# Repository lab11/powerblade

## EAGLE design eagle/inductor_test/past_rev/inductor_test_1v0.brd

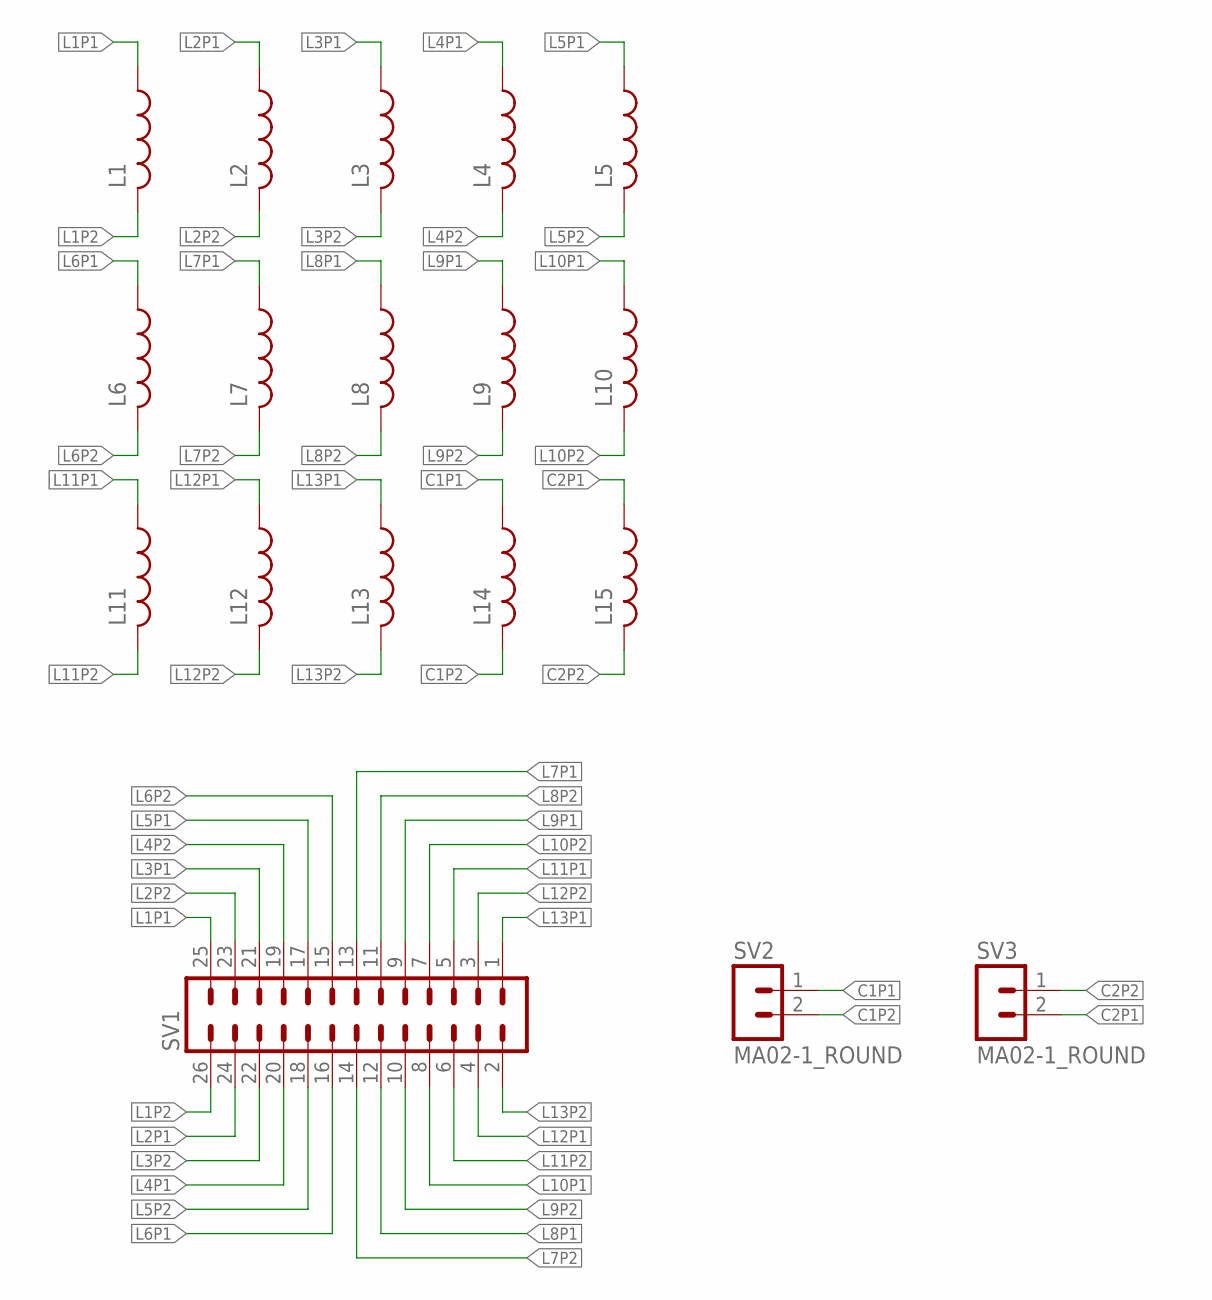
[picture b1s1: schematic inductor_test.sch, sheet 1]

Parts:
L1, L2, L3, L4, L5, L6, L7, L8, L9, L10, L11, L12, L13, L14, L15: L-USL0805; L0805
SV1: MA13-2BARE; MA13-2_BARE; DIGIKEY 3M9464-ND
SV2, SV3: MA02-1_ROUND; DIGIKEY NP

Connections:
C1P1: L14.1, SV2.1
C1P2: L14.2, SV2.2
C2P1: L15.1, SV3.2
C2P2: L15.2, SV3.1
L1P1: L1.1, SV1.25
L1P2: L1.2, SV1.26
L2P1: L2.1, SV1.24
L2P2: L2.2, SV1.23
L3P1: L3.1, SV1.21
L3P2: L3.2, SV1.22
L4P1: L4.1, SV1.20
L4P2: L4.2, SV1.19
L5P1: L5.1, SV1.17
L5P2: L5.2, SV1.18
L6P1: L6.1, SV1.16
L6P2: L6.2, SV1.15
L7P1: L7.1, SV1.13
L7P2: L7.2, SV1.14
L8P1: L8.1, SV1.12
L8P2: L8.2, SV1.11
L9P1: L9.1, SV1.9
L9P2: L9.2, SV1.10
L10P1: L10.1, SV1.8
L10P2: L10.2, SV1.7
L11P1: L11.1, SV1.5
L11P2: L11.2, SV1.6
L12P1: L12.1, SV1.4
L12P2: L12.2, SV1.3
L13P1: L13.1, SV1.1
L13P2: L13.2, SV1.2

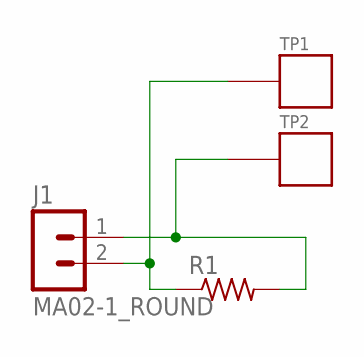
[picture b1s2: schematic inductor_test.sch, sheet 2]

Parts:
J1: MA02-1_ROUND; DIGIKEY NP
R1: R-US_R0603; R0603; DIGIKEY P49.9HCT-ND
TP1, TP2: TP_STD; TP; DIGIKEY NP

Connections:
unnamed: J1.2, R1.1, TP1.P$1
unnamed: J1.1, R1.2, TP2.P$1

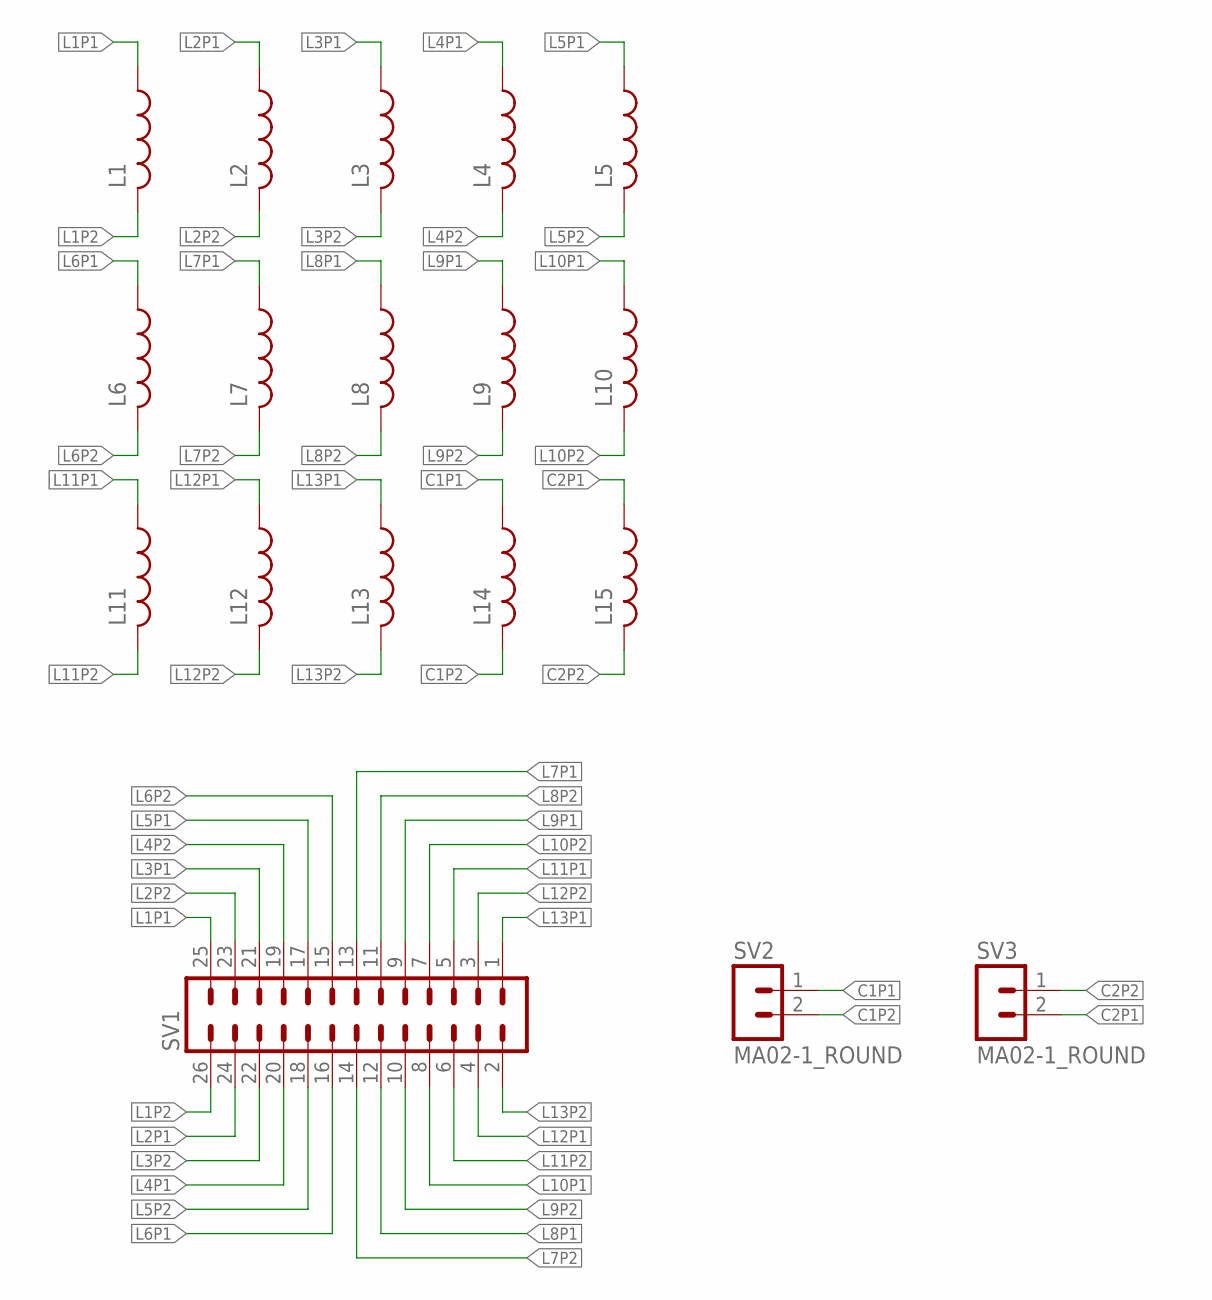
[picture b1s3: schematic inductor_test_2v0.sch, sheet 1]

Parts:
L1, L2, L3, L4, L5, L6, L7, L8, L9, L10, L11, L12, L13, L14, L15: L-USL0805; L0805
SV1: MA13-2BARE; MA13-2_BARE; DIGIKEY 3M9464-ND
SV2, SV3: MA02-1_ROUND; DIGIKEY NP

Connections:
C1P1: L14.1, SV2.1
C1P2: L14.2, SV2.2
C2P1: L15.1, SV3.2
C2P2: L15.2, SV3.1
L1P1: L1.1, SV1.25
L1P2: L1.2, SV1.26
L2P1: L2.1, SV1.24
L2P2: L2.2, SV1.23
L3P1: L3.1, SV1.21
L3P2: L3.2, SV1.22
L4P1: L4.1, SV1.20
L4P2: L4.2, SV1.19
L5P1: L5.1, SV1.17
L5P2: L5.2, SV1.18
L6P1: L6.1, SV1.16
L6P2: L6.2, SV1.15
L7P1: L7.1, SV1.13
L7P2: L7.2, SV1.14
L8P1: L8.1, SV1.12
L8P2: L8.2, SV1.11
L9P1: L9.1, SV1.9
L9P2: L9.2, SV1.10
L10P1: L10.1, SV1.8
L10P2: L10.2, SV1.7
L11P1: L11.1, SV1.5
L11P2: L11.2, SV1.6
L12P1: L12.1, SV1.4
L12P2: L12.2, SV1.3
L13P1: L13.1, SV1.1
L13P2: L13.2, SV1.2

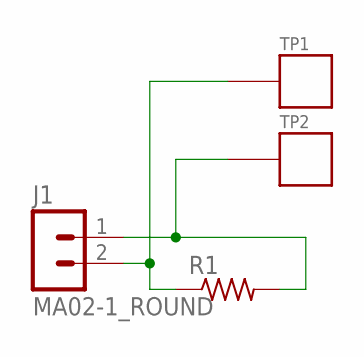
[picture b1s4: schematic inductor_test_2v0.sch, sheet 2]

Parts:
J1: MA02-1_ROUND; DIGIKEY NP
R1: R-US_R0603; R0603; DIGIKEY P49.9HCT-ND
TP1, TP2: TP_STD; TP; DIGIKEY NP

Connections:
unnamed: J1.2, R1.1, TP1.P$1
unnamed: J1.1, R1.2, TP2.P$1

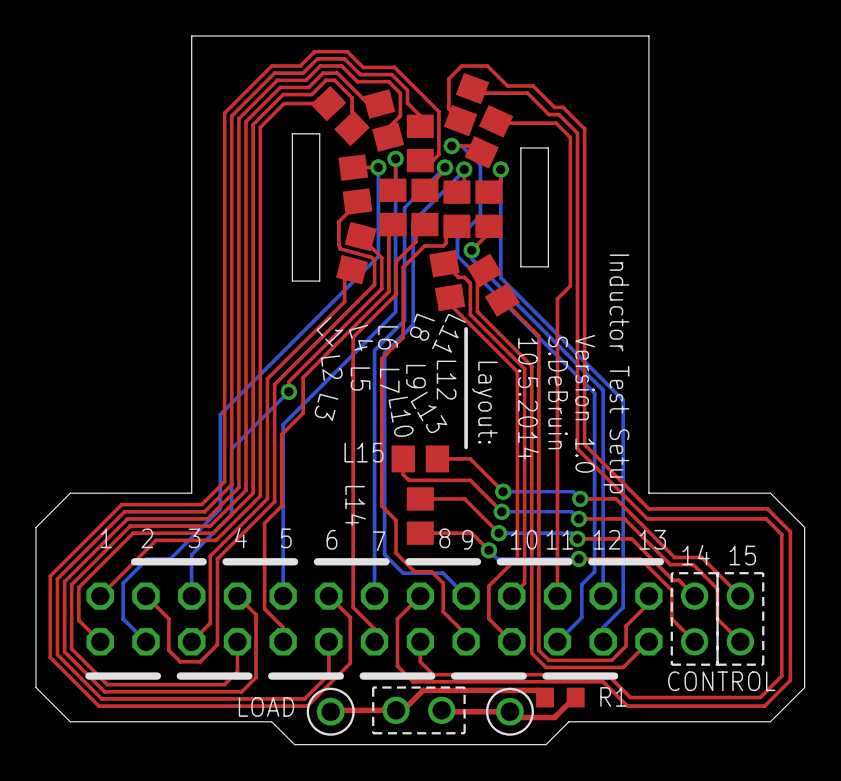
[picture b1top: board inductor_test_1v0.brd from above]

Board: 2 copper layers, 42.7 x 39.4 mm, 23 parts (0 on the bottom side), 32 nets.

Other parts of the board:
U$1: NEMA_1-15_TIGHT

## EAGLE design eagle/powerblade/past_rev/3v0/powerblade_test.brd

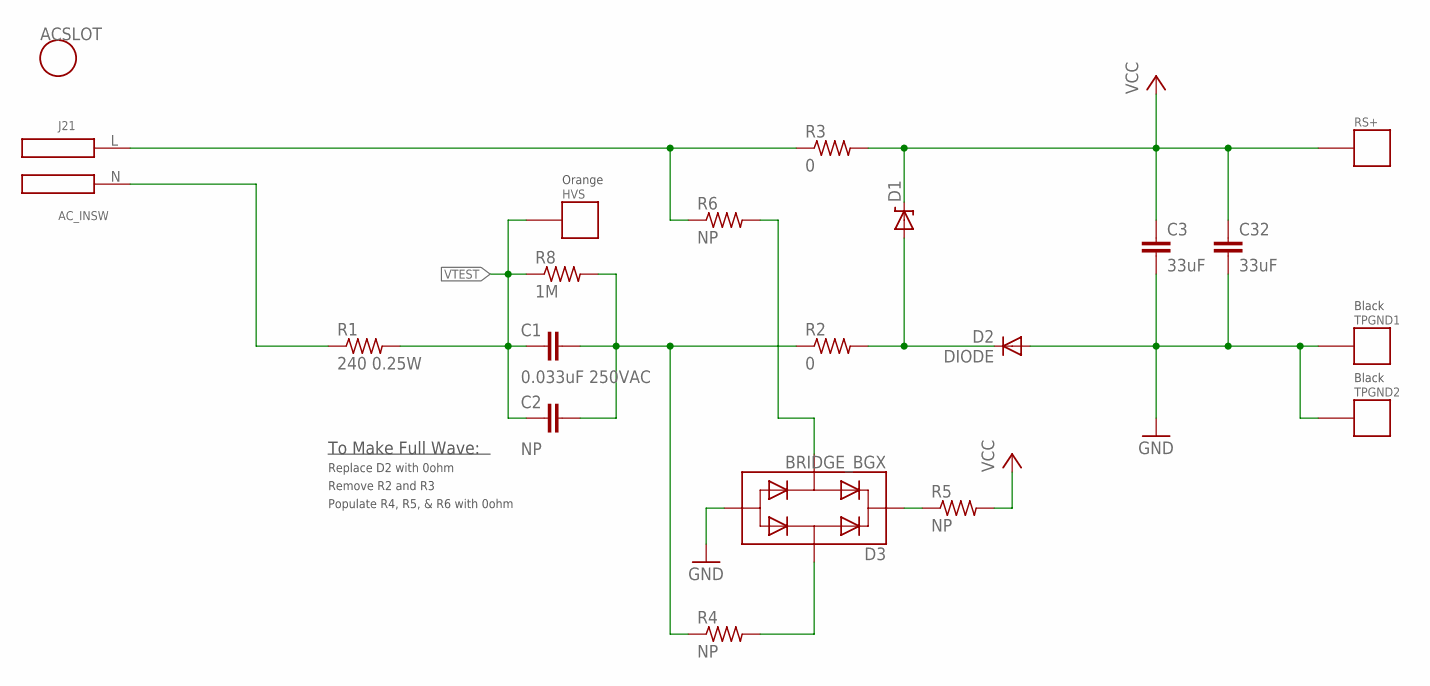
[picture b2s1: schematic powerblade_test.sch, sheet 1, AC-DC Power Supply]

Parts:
ACSLOT: AC_NODIM; AC3_NODIM; DIGIKEY NP
C1: 0.033uF 250VAC; C2220K; DIGIKEY 490-5919-1-ND
C2: NP; C2220K; DIGIKEY NP
C3, C32: 33uF; C0603; DIGIKEY 718-1672-1-ND
D1: ZENERBZT52; BZT52; DIGIKEY NP
D2: DIODE; BAS521; DIGIKEY NP
D3: BRIDGE_BGX; TO-253-4; DIGIKEY NP
HVS: TP_MULT; DIGIKEY 5013K-ND
J21: AC_INSW; AC_DC21; DIGIKEY NP
R1: 240 0.25W; R0603; DIGIKEY RHM240DCT-ND
R2, R3: 0; R0603; DIGIKEY P0.0GCT-ND
R4, R5, R6: NP; R0603; DIGIKEY NP
R8: 1M; R0603; DIGIKEY MCT0603-1.00M-CFCT-ND
RS+: TP_MULT; DIGIKEY 5014K-ND
TPGND1, TPGND2: TP_MULT; DIGIKEY 5011K-ND

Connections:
GND: C3.2, C32.2, D2.A, D3.P3, TPGND1.P$1, TPGND2.P$1; also elsewhere on the board
N: J21.N, R1.1
unnamed: D1.A, D2.C, R2.2
unnamed: C1.1, C2.1, R2.1, R4.1, R8.2
unnamed: D3.P4, R4.2
unnamed: D3.P1, R5.1
unnamed: D3.P2, R6.2
P: J21.L, R3.1, R6.1
VCC: C3.1, C32.1, D1.C, R3.2, R5.2, RS+.P$1; also elsewhere on the board
VTEST: C1.2, C2.2, HVS.P$1, R1.2, R8.1; also elsewhere on the board

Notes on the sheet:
To Make Full Wave:
Replace D2 with 0ohm
Remove R2 and R3
Populate R4, R5, & R6 with 0ohm
Orange
Black

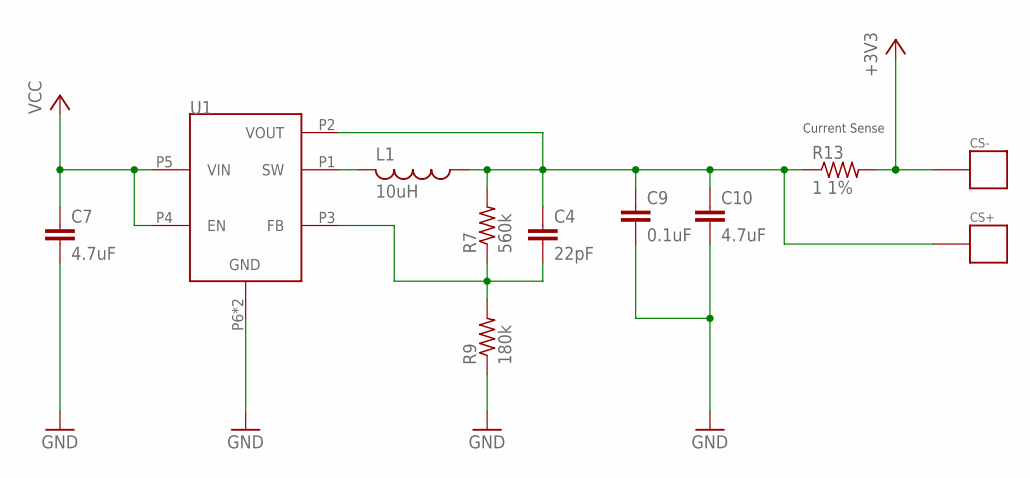
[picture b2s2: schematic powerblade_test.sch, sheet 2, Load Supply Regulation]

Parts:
C4: 22pF; C0402; DIGIKEY 1276-1116-1-ND
C7: 4.7uF; C0603; DIGIKEY 1276-1784-1-ND
C9: 0.1uF; C0402; DIGIKEY 1276-1001-1-ND
C10: 4.7uF; C0402; DIGIKEY 490-5915-1-ND
CS+: TP_MULT; DIGIKEY 5012K-ND
CS-: TP_MULT; DIGIKEY 5010K-ND
L1: 10uH; L0805; DIGIKEY 490-4990-1-ND
R7: 560k; R0402; DIGIKEY P560KLCT-ND
R9: 180k; R0402; DIGIKEY P180KLCT-ND
R13: 1 1%; R0603; DIGIKEY P1.0AJCT-ND
U1: TPS62122; WDFN-6

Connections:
+3V3: CS-.P$1, R13.2; also elsewhere on the board
GND: C7.2, C9.2, C10.2, R9.1, U1.P6 (GND), U1.PAD (GND); also elsewhere on the board
unnamed: L1.2, U1.P1 (SW)
unnamed: C4.1, C9.1, C10.1, CS+.P$1, L1.1, R7.2, R13.1, U1.P2 (VOUT)
unnamed: C4.2, R7.1, R9.2, U1.P3 (FB)
VCC: C7.1, U1.P4 (EN), U1.P5 (VIN); also elsewhere on the board

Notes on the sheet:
Current Sense

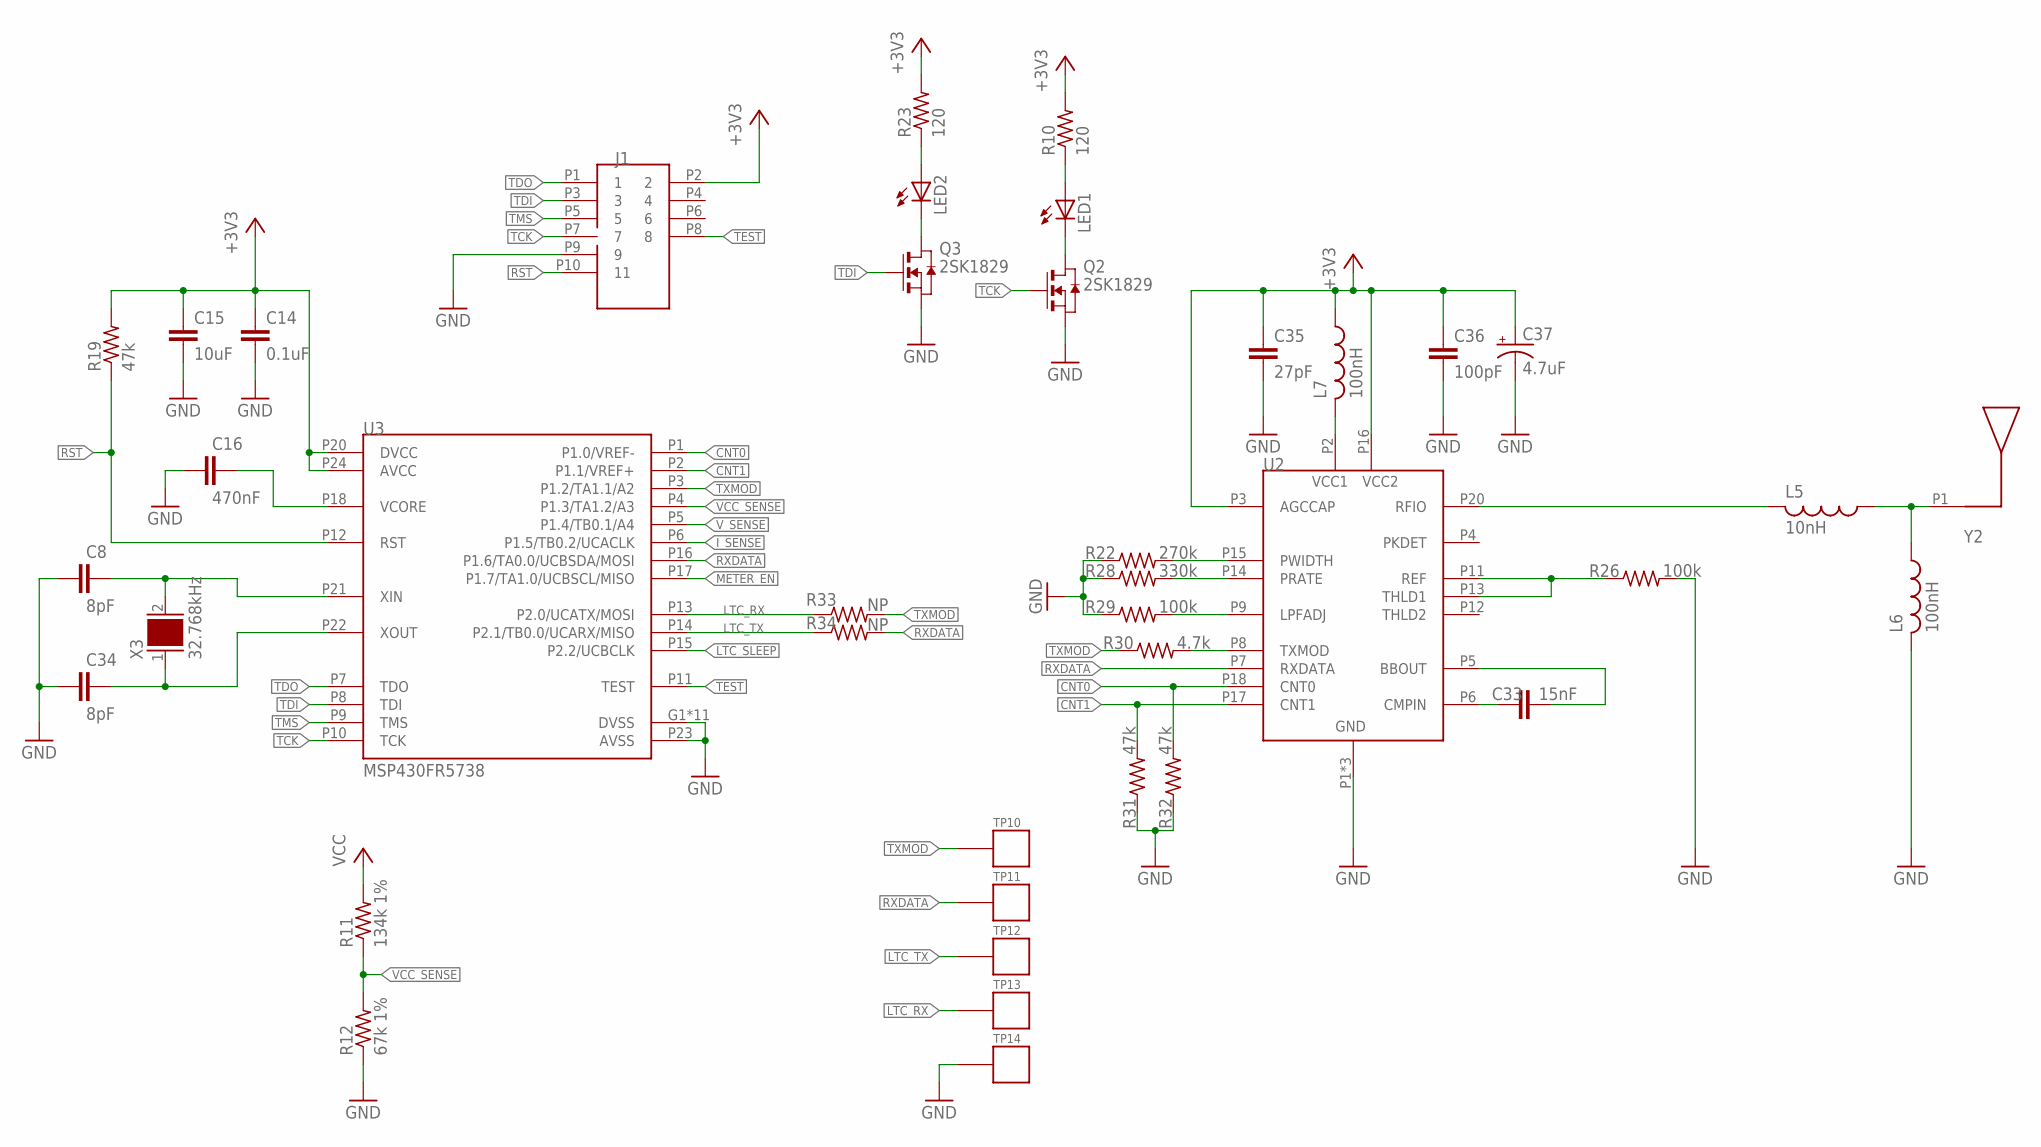
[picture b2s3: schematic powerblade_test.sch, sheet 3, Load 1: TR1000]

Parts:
C8, C34: 8pF; C0603; DIGIKEY 1276-1817-1-ND
C14: 0.1uF; C0603; DIGIKEY 445-1316-1-ND
C15: 10uF; C0603; DIGIKEY 1276-1119-1-ND
C16: 470nF; C0603; DIGIKEY 445-5192-1-ND
C33: 15nF; C0603; DIGIKEY 445-5091-1-ND
C35: 27pF; C0603; DIGIKEY 445-1274-1-ND
C36: 100pF; C0603; DIGIKEY 445-1281-1-ND
C37: 4.7uF; CPOL-0805; DIGIKEY 478-8120-1-ND
J1: JTAG_14PIN_IDC; TC2050-IDC-430; DIGIKEY NP
L5: 10nH; L0402; DIGIKEY 732-2924-1-ND
L6: 100nH; L0402; DIGIKEY CW100505-R10JCT-ND
L7: 100nH; L0603; DIGIKEY 587-1566-1-ND
LED1, LED2: LED0603; LED-0603; DIGIKEY 160-1183-1-ND
Q2, Q3: 2SK1829; SC-70-3
R10, R23: 120; R0603; DIGIKEY P120GCT-ND
R11: 134k 1%; R0603; DIGIKEY P133KHCT-ND
R12: 67k 1%; R0603; DIGIKEY P66.5KHCT-ND
R19, R31, R32: 47k; R0603; DIGIKEY P47KGCT-ND
R22: 270k; R0603; DIGIKEY P270KGCT-ND
R26, R29: 100k; R0603; DIGIKEY P100KGCT-ND
R28: 330k; R0603; DIGIKEY P330KGCT-ND
R30: 4.7k; R0603; DIGIKEY P4.7KGCT-ND
R33, R34: NP; R0603; DIGIKEY NP
TP10, TP11, TP12, TP13, TP14: TP_STD; TP; DIGIKEY NP
U2: TR1000; SM-20H
U3: MSP430FR5738; VQFN-24
X3: 32.768kHz; 0805; DIGIKEY 535-12373-1-ND
Y2: ANT-916

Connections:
+3V3: C14.1, C15.1, C35.1, C36.1, C37.+, J1.P2 (2), L7.1, R10.2, R19.2, R23.2, U2.P3 (AGCCAP), U2.P16 (VCC2), U3.P20 (DVCC), U3.P24 (AVCC); also elsewhere on the board
CNT0: R32.2, U2.P18 (CNT0), U3.P1 (P1.0/VREF-)
CNT1: R31.2, U2.P17 (CNT1), U3.P2 (P1.1/VREF+)
GND: C8.1, C14.2, C15.2, C16.1, C34.1, C35.2, C36.2, C37.-, J1.P9 (9), L6.2, Q2.P2 (S), Q3.P2 (S), R12.1, R22.1, R26.2, R28.1, R29.1, R31.1, R32.1, TP14.P$1, U2.P1 (GND), U2.P10 (GND), U2.P19 (GND), U3.G1 (DVSS), U3.G2 (DVSS), U3.G3 (DVSS), U3.G4 (DVSS), U3.G5 (DVSS), U3.G6 (DVSS), U3.G7 (DVSS), U3.G8 (DVSS), U3.G9 (DVSS), U3.P19 (DVSS), U3.P23 (AVSS), U3.PAD (DVSS); also elsewhere on the board
I_SENSE: U3.P6 (P1.5/TB0.2/UCACLK); also elsewhere on the board
LTC_RX: R33.1, TP13.P$1, U3.P13 (P2.0/UCATX/MOSI); also elsewhere on the board
LTC_SLEEP: U3.P15 (P2.2/UCBCLK); also elsewhere on the board
LTC_TX: R34.1, TP12.P$1, U3.P14 (P2.1/TB0.0/UCARX/MISO); also elsewhere on the board
METER_EN: U3.P17 (P1.7/TA1.0/UCBSCL/MISO); also elsewhere on the board
unnamed: C34.2, U3.P22 (XOUT), X3.1
unnamed: C33.2, U2.P5 (BBOUT)
unnamed: L7.2, U2.P2 (VCC1)
unnamed: C16.2, U3.P18 (VCORE)
unnamed: LED1.A, R10.1
unnamed: R22.2, U2.P15 (PWIDTH)
unnamed: R28.2, U2.P14 (PRATE)
unnamed: R29.2, U2.P9 (LPFADJ)
unnamed: R30.2, U2.P8 (TXMOD)
unnamed: LED1.C, Q2.P3 (D)
unnamed: C33.1, U2.P6 (CMPIN)
unnamed: C8.2, U3.P21 (XIN), X3.2
unnamed: R26.1, U2.P11 (REF), U2.P13 (THLD1)
unnamed: LED2.A, R23.1
unnamed: LED2.C, Q3.P3 (D)
unnamed: L5.2, U2.P20 (RFIO)
unnamed: L5.1, L6.1, Y2.P1
RST: J1.P10 (11), R19.1, U3.P12 (RST)
RXDATA: R34.2, TP11.P$1, U2.P7 (RXDATA), U3.P16 (P1.6/TA0.0/UCBSDA/MOSI)
TCK: J1.P7 (7), Q2.P1 (G), U3.P10 (TCK)
TDI: J1.P3 (3), Q3.P1 (G), U3.P8 (TDI)
TDO: J1.P1 (1), U3.P7 (TDO)
TEST: J1.P8 (8), U3.P11 (TEST)
TMS: J1.P5 (5), U3.P9 (TMS)
TXMOD: R30.1, R33.2, TP10.P$1, U3.P3 (P1.2/TA1.1/A2)
VCC: R11.2; also elsewhere on the board
VCC_SENSE: R11.1, R12.2, U3.P4 (P1.3/TA1.2/A3)
V_SENSE: U3.P5 (P1.4/TB0.1/A4); also elsewhere on the board

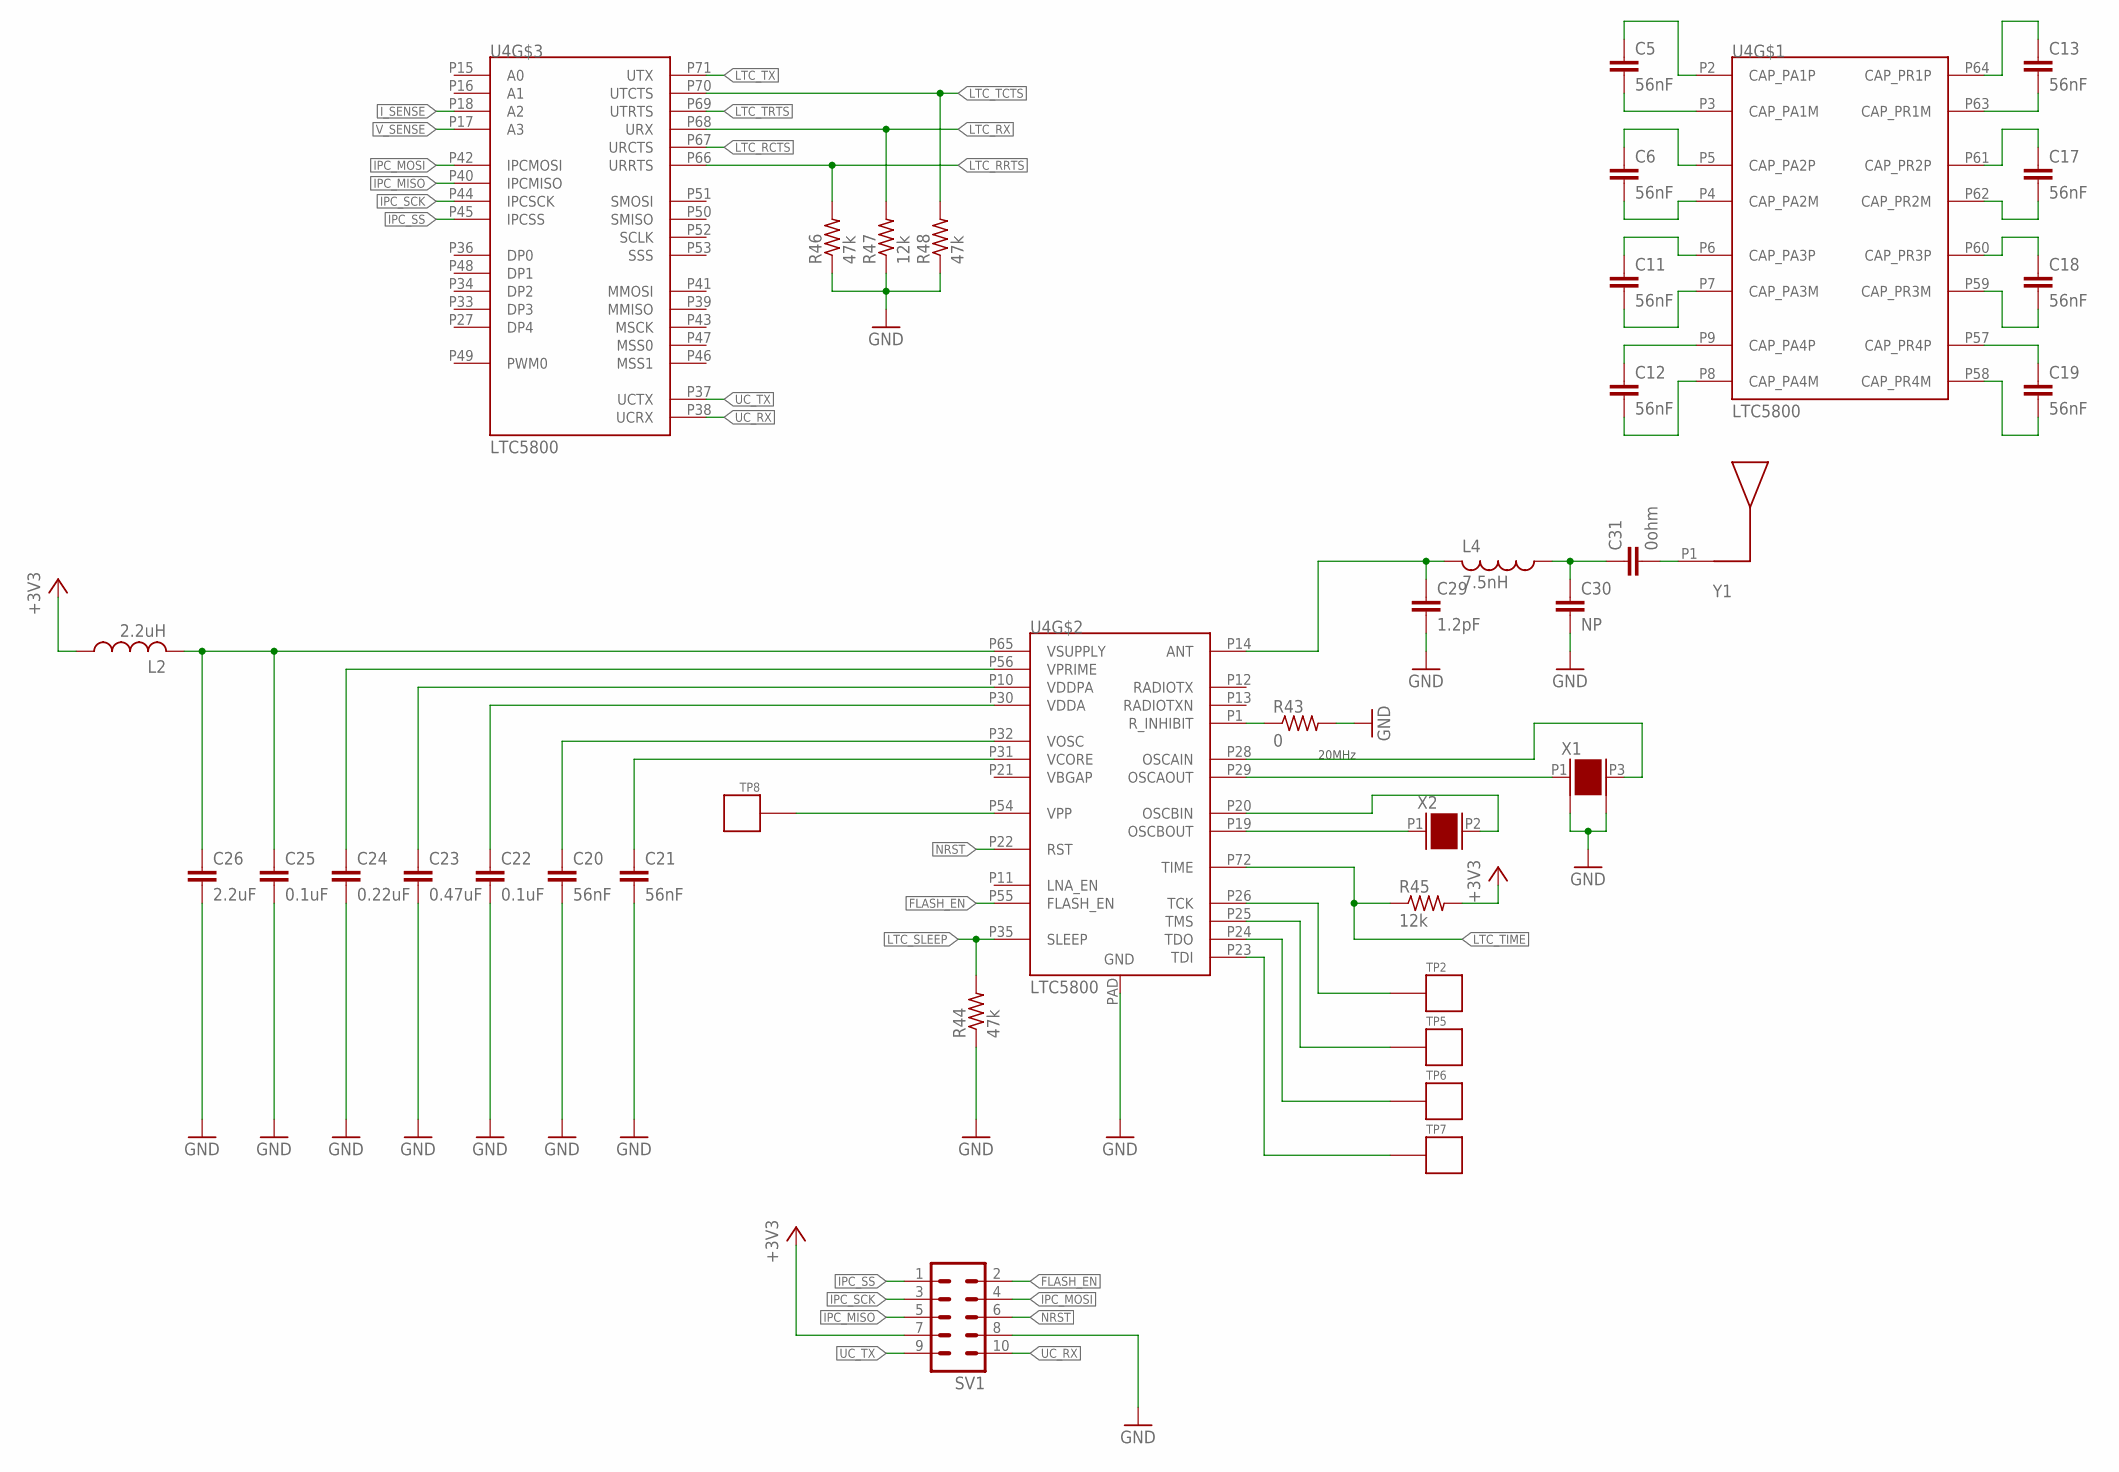
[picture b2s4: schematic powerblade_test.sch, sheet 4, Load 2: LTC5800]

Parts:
C5, C6, C11, C12, C13, C17, C18, C19, C20, C21: 56nF; C0402; DIGIKEY 490-6324-1-ND
C22, C25: 0.1uF; C0603; DIGIKEY 445-1316-1-ND
C23: 0.47uF; C0603; DIGIKEY 1276-2377-1-ND
C24: 0.22uF; C0603; DIGIKEY 445-1318-1-ND
C26: 2.2uF; C0603; DIGIKEY 1276-2368-1-ND
C29: 1.2pF; C0402; DIGIKEY 490-6209-1-ND
C30: NP; C0402; DIGIKEY NP
C31: 0ohm; C0402; DIGIKEY P0.0JCT-ND
L2: 2.2uH; L0603; DIGIKEY 490-4023-1-ND
L4: 7.5nH; L0402; DIGIKEY 490-6760-1-ND
R43: 0; R0402; DIGIKEY P0.0JCT-ND
R44, R46, R48: 47k; R0402; DIGIKEY P47KJCT-ND
R45, R47: 12k; R0402; DIGIKEY P12KJCT-ND
SV1: MA05-2KEY; MA05-2_KEY
TP2, TP5, TP6, TP7: TP_SMD; DIGIKEY NP
TP8: TP_STD; TP; DIGIKEY NP
U4: LTC5800; QFN-72
X1: ABM8G
X2: ABS07
Y1: UREACH_XTEND

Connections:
+3V3: L2.1, R45.2, SV1.7; also elsewhere on the board
FLASH_EN: SV1.2, U4.P55 (FLASH_EN)
GND: C20.2, C21.2, C22.2, C23.2, C24.2, C25.2, C26.2, C29.2, C30.2, R43.2, R44.1, R46.1, R47.1, R48.1, SV1.8, U4.PAD (GND), X1.P2 (G1), X1.P4 (G2); also elsewhere on the board
IPC_MISO: SV1.5, U4.P40 (IPCMISO)
IPC_MOSI: SV1.4, U4.P42 (IPCMOSI)
IPC_SCK: SV1.3, U4.P44 (IPCSCK)
IPC_SS: SV1.1, U4.P45 (IPCSS)
I_SENSE: U4.P18 (A2); also elsewhere on the board
LTC_RCTS: U4.P67 (URCTS)
LTC_RRTS: R46.2, U4.P66 (URRTS)
LTC_RX: R47.2, U4.P68 (URX); also elsewhere on the board
LTC_SLEEP: R44.2, U4.P35 (SLEEP); also elsewhere on the board
LTC_TCTS: R48.2, U4.P70 (UTCTS)
LTC_TIME: R45.1, U4.P72 (TIME)
LTC_TRTS: U4.P69 (UTRTS)
LTC_TX: U4.P71 (UTX); also elsewhere on the board
unnamed: C5.1, U4.P2 (CAP_PA1P)
unnamed: C5.2, U4.P3 (CAP_PA1M)
unnamed: C6.1, U4.P5 (CAP_PA2P)
unnamed: C6.2, U4.P4 (CAP_PA2M)
unnamed: C11.1, U4.P6 (CAP_PA3P)
unnamed: C11.2, U4.P7 (CAP_PA3M)
unnamed: C12.1, U4.P9 (CAP_PA4P)
unnamed: C12.2, U4.P8 (CAP_PA4M)
unnamed: C13.1, U4.P64 (CAP_PR1P)
unnamed: C13.2, U4.P63 (CAP_PR1M)
unnamed: C17.1, U4.P61 (CAP_PR2P)
unnamed: C17.2, U4.P62 (CAP_PR2M)
unnamed: C18.1, U4.P60 (CAP_PR3P)
unnamed: C18.2, U4.P59 (CAP_PR3M)
unnamed: C19.1, U4.P57 (CAP_PR4P)
unnamed: C19.2, U4.P58 (CAP_PR4M)
unnamed: C21.1, U4.P31 (VCORE)
unnamed: C20.1, U4.P32 (VOSC)
unnamed: C25.1, C26.1, L2.2, U4.P65 (VSUPPLY)
unnamed: C24.1, U4.P56 (VPRIME)
unnamed: C23.1, U4.P10 (VDDPA)
unnamed: C22.1, U4.P30 (VDDA)
unnamed: U4.P29 (OSCAOUT), X1.P1
unnamed: U4.P28 (OSCAIN), X1.P3 (P2)
unnamed: U4.P20 (OSCBIN), X2.P2
unnamed: U4.P19 (OSCBOUT), X2.P1
unnamed: C29.1, L4.2, U4.P14 (ANT)
unnamed: C30.1, C31.1, L4.1
unnamed: C31.2, Y1.P1
unnamed: TP8.P$1, U4.P54 (VPP)
unnamed: TP7.P$1, U4.P23 (TDI)
unnamed: TP6.P$1, U4.P24 (TDO)
unnamed: TP5.P$1, U4.P25 (TMS)
unnamed: TP2.P$1, U4.P26 (TCK)
unnamed: R43.1, U4.P1 (R_INHIBIT)
NRST: SV1.6, U4.P22 (RST)
UC_RX: SV1.10, U4.P38 (UCRX)
UC_TX: SV1.9, U4.P37 (UCTX)
V_SENSE: U4.P17 (A3); also elsewhere on the board

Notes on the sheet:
20MHz

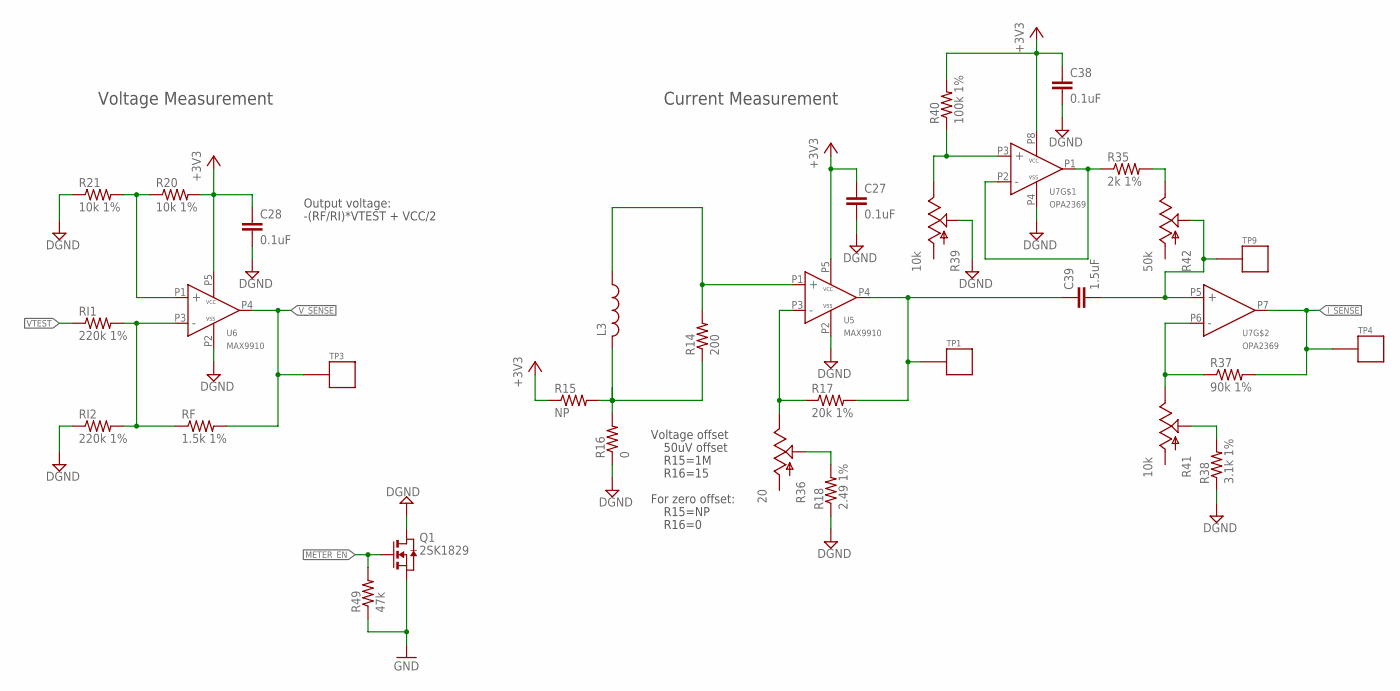
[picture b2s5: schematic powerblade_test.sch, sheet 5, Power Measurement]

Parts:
C27, C28, C38: 0.1uF; C0402; DIGIKEY 445-1265-1-ND
C39: 1.5uF; C0402; DIGIKEY 445-13874-1-ND
L3: L-USL0805; L0805; DIGIKEY 732-3452-1-ND
Q1: 2SK1829; SC-70-3
R14: 200; R0402; DIGIKEY P200LCT-ND
R15: NP; R0402; DIGIKEY NP
R16: 0; R0402; DIGIKEY P0.0JCT-ND
R17: 20k 1%; R0402; DIGIKEY P20.0KLCT-ND
R18: 2.49 1%; R0402; DIGIKEY 541-2.49LLCT-ND
R20, R21: 10k 1%; R0402; DIGIKEY P10.0KLCT-ND
R35: 2k 1%; R0402; DIGIKEY P2.00KLCT-ND
R36: 20; 3313_POT; DIGIKEY 3313J-1-200ECT-ND
R37: 90k 1%; R0402; DIGIKEY P90.9KLCT-ND
R38: 3.1k 1%; R0603; DIGIKEY P3.09KHCT-ND
R39, R41: 10k; 3313_POT; DIGIKEY 3313J-103ECT-ND
R40: 100k 1%; R0402; DIGIKEY P100KLCT-ND
R42: 50k; 3313_POT; DIGIKEY 3313J-503ECT-ND
R49: 47k; R0603; DIGIKEY P47KGCT-ND
RF: 1.5k 1%; R0402; DIGIKEY P1.50KLCT-ND
RI1, RI2: 220k 1%; R0402; DIGIKEY P220KLCT-ND
TP1, TP4, TP9: TP_MULT; DIGIKEY 5126K-ND
TP3: TP_MULT; DIGIKEY 5129K-ND
U5, U6: MAX9910; SC70-5
U7: OPA2369; SOT-23-8

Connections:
+3V3: C27.1, C28.1, C38.1, R15.1, R20.2, R40.2, U5.P5 (VCC), U6.P5 (VCC), U7.P8 (VCC); also elsewhere on the board
DGND: C27.2, C28.2, C38.2, Q1.P3 (D), R16.1, R18.1, R21.1, R38.1, R39.PW, RI2.1, U5.P2 (VSS), U6.P2 (VSS), U7.P4 (VSS)
GND: Q1.P2 (S), R49.1; also elsewhere on the board
I_SENSE: R37.2, TP4.P$1, U7.P7 (OUT); also elsewhere on the board
METER_EN: Q1.P1 (G), R49.2; also elsewhere on the board
unnamed: L3.2, R14.1, R15.2, R16.2
unnamed: L3.1, R14.2, U5.P1 (IN+)
unnamed: R17.1, R36.P2, U5.P3 (IN-)
unnamed: R20.1, R21.2, U6.P1 (IN+)
unnamed: RF.1, RI1.2, RI2.2, U6.P3 (IN-)
unnamed: C39.1, R17.2, TP1.P$1, U5.P4 (OUT)
unnamed: R18.2, R36.PW
unnamed: R37.1, R41.P2, U7.P6 (IN-)
unnamed: C39.2, R42.PW, TP9.P$1, U7.P5 (IN+)
unnamed: R35.1, U7.P1 (OUT), U7.P2 (IN-)
unnamed: R38.2, R41.PW
unnamed: R39.P2, R40.1, U7.P3 (IN+)
unnamed: R35.2, R42.P2
VTEST: RI1.1; also elsewhere on the board
V_SENSE: RF.2, TP3.P$1, U6.P4 (OUT); also elsewhere on the board

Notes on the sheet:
Voltage offset
50uV offset
For zero offset:
R15=NP
R16=0
Current Measurement
Voltage Measurement
Output voltage:
-(RF/RI)*VTEST + VCC/2
R15=1M
R16=15

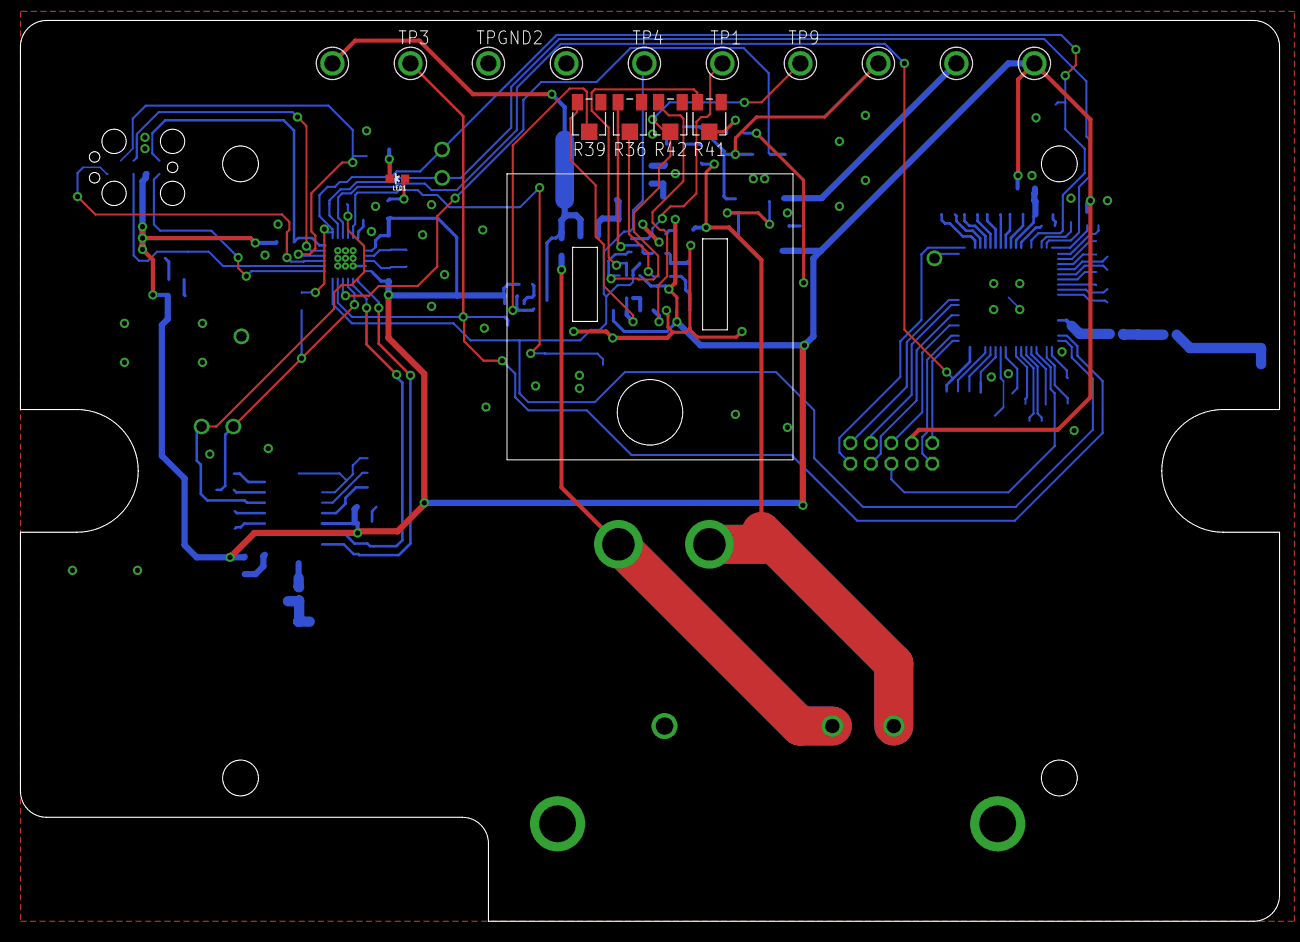
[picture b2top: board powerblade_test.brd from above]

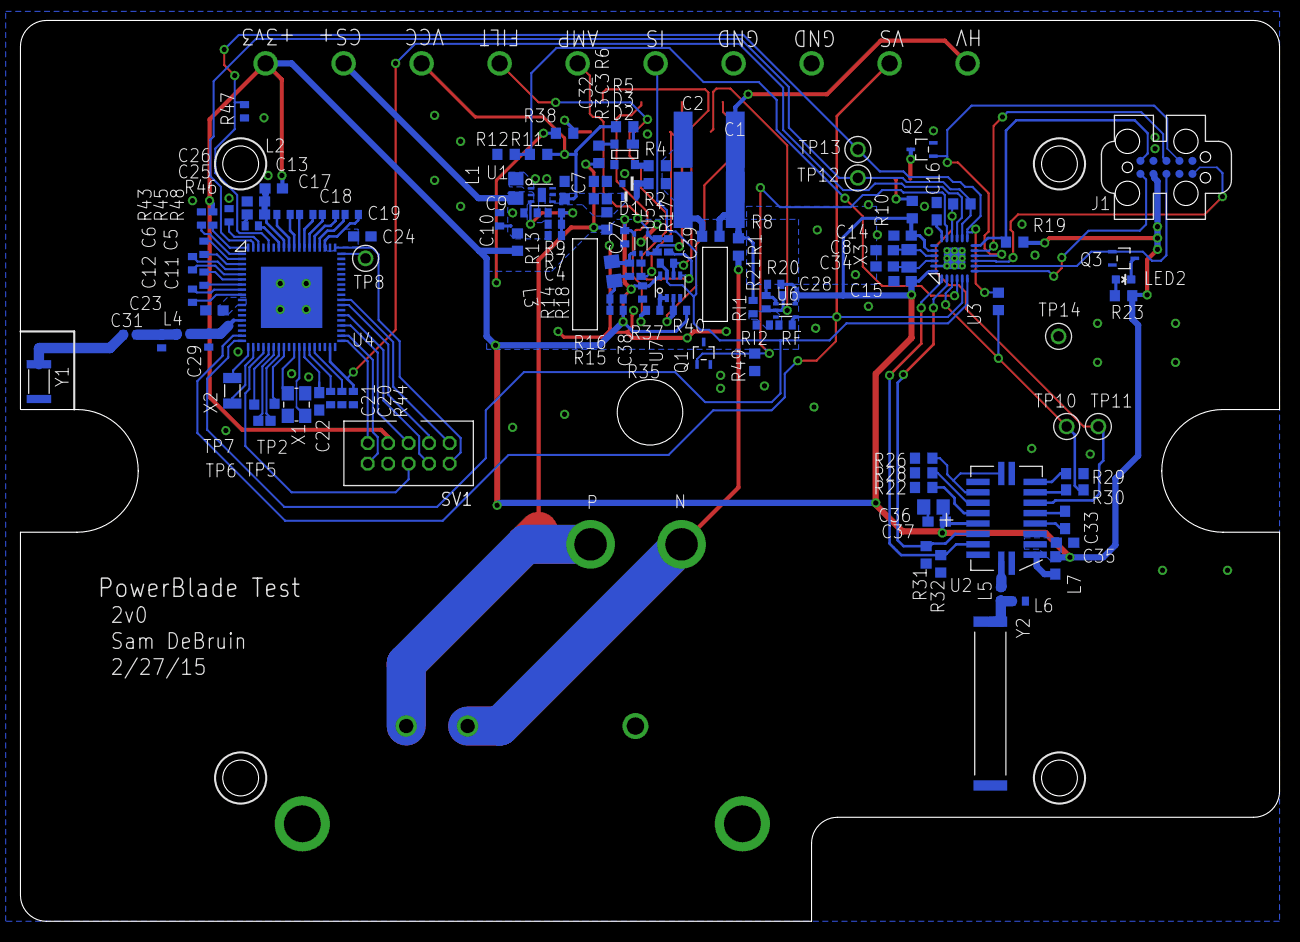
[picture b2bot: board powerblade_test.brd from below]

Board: 2 copper layers, 123.0 x 88.0 mm, 139 parts (123 on the bottom side), 108 nets.

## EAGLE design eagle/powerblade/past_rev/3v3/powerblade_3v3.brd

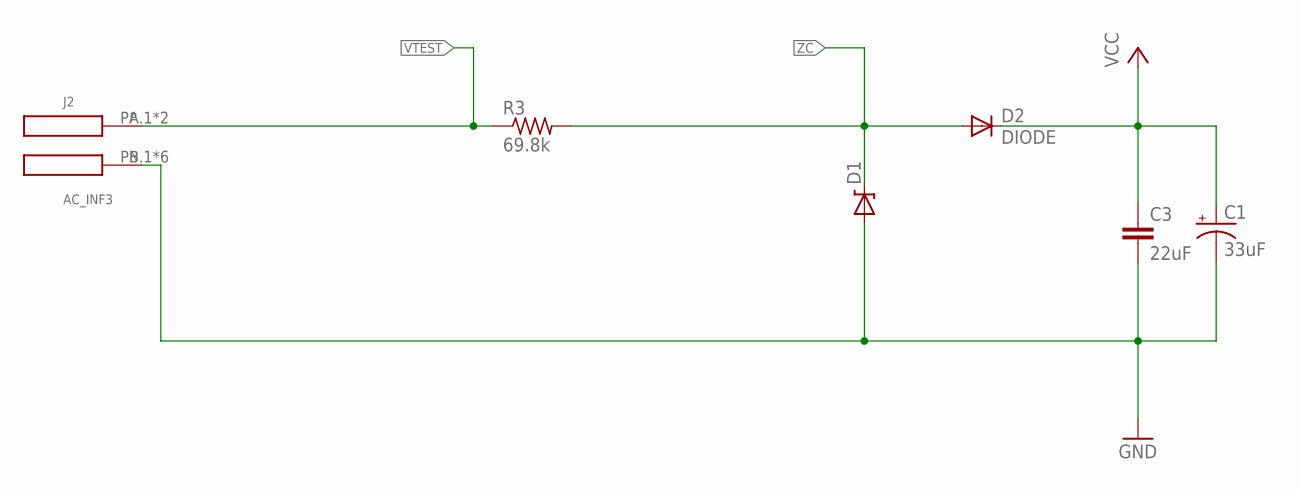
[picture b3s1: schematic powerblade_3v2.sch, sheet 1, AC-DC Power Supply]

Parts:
C1: 33uF; CPOL0805_SM; DIGIKEY 478-8650-1-ND
C3: 22uF; C0603_SM; DIGIKEY 445-9077-1-ND
D1: ZENERBZT52; BZT52; DIGIKEY BZT52C10T-7DICT-ND
D2: DIODE; BAS521
J2: AC_INF3; AC3_F3; DIGIKEY ED1649-ND
R3: 69.8k; R1210; DIGIKEY P69.8KAACT-ND

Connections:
VCC: C1.+, C3.1, D2.C; also elsewhere on the board
VTEST: J2.PA.1, J2.PA.3, R3.1; also elsewhere on the board
ZC: D1.C, D2.A, R3.2; also elsewhere on the board

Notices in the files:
parts and their libraries:
SparkFun-LED: Licensing: CC v3.0 Share-Alike You are welcome to use this library for commercial purposes.
